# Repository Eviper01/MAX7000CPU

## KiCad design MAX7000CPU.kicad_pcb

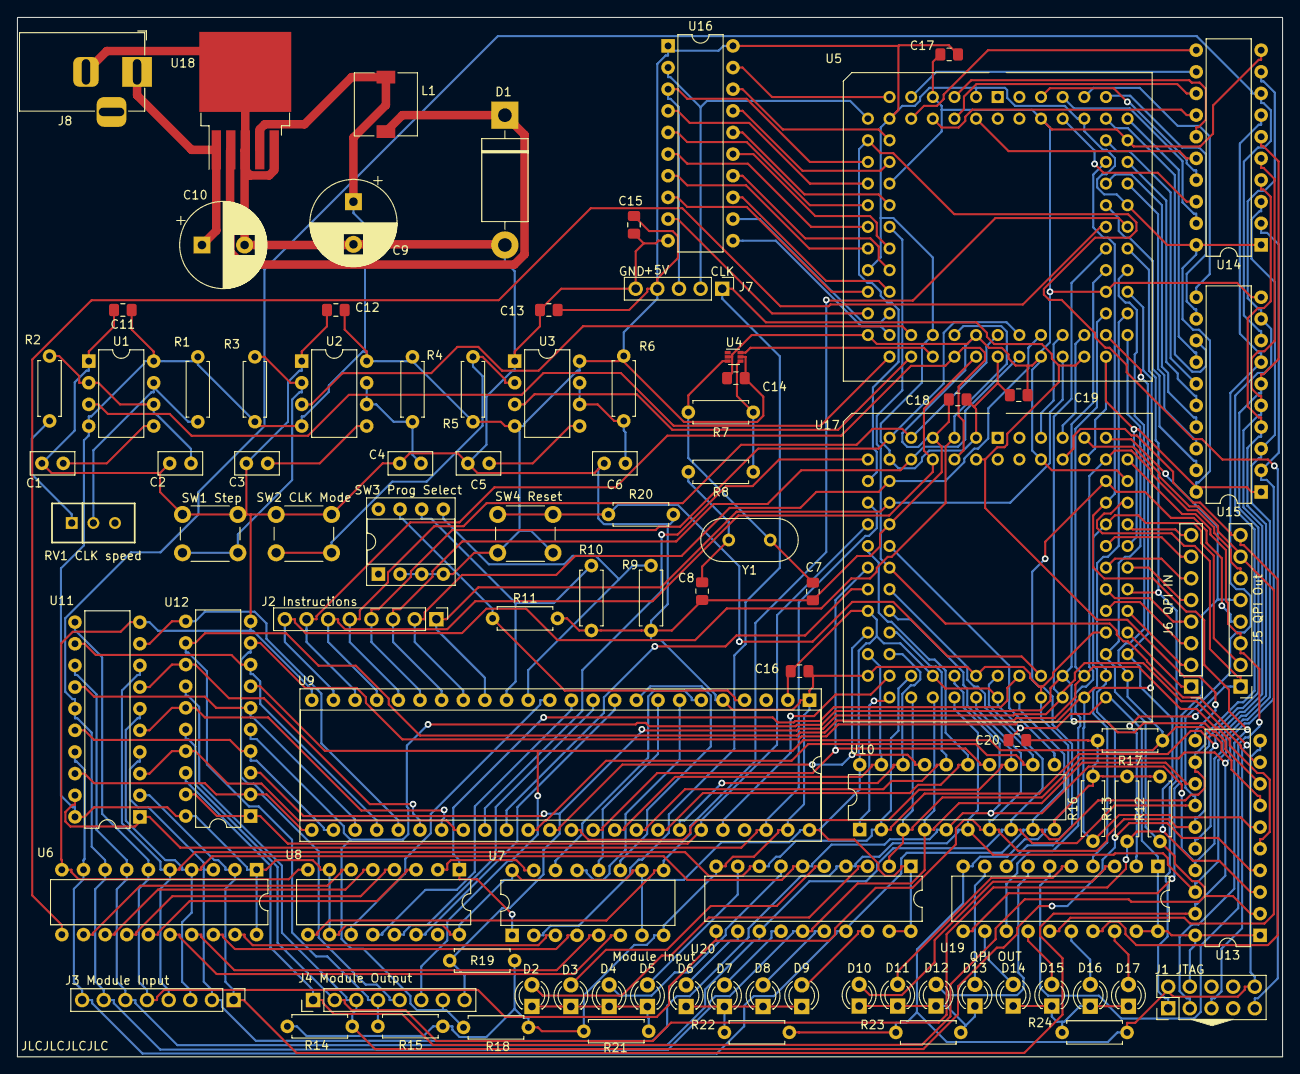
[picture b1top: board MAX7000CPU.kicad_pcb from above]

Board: 2 copper layers, 148.5 x 122.0 mm, 96 parts (0 on the bottom side), 170 nets.

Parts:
C1, C2, C3, C5: 10n; C_Disc_D5.0mm_W2.5mm_P2.50mm
C4, C6: 100n; C_Disc_D5.0mm_W2.5mm_P2.50mm
C7, C8: 32p; C_0805_2012Metric_Pad1.18x1.45mm_HandSolder
C9: 220u; CP_Radial_D10.0mm_P5.00mm
C10: 680u; CP_Radial_D10.0mm_P5.00mm
C11, C12, C13, C14, C15, C16, C17, C18, C19, C20: 100n; C_0805_2012Metric_Pad1.18x1.45mm_HandSolder
D1: 1N5822; D_DO-201AD_P15.24mm_Horizontal
D2, D3, D4, D5, D6, D7, D8, D9, D10, D11, D12, D13, D14, D15, D16, D17: LED; LED_D3.0mm
J1 JTAG: Conn_02x05_Odd_Even; PinHeader_2x05_P2.54mm_Vertical
J2 Instructions, J3 Module Input, J4 Module Output, J5 QPI Out, J6 QPI IN: Conn_01x08_Male; PinHeader_1x08_P2.54mm_Vertical
J7: Conn_01x05_Male; PinHeader_1x05_P2.54mm_Vertical
J8: Barrel_Jack; BarrelJack_Horizontal
L1: 33u; L_7.3x7.3_H3.5
R1, R2, R3, R5, R8: 1K; R_Axial_DIN0207_L6.3mm_D2.5mm_P7.62mm_Horizontal
R4, R6: 1M; R_Axial_DIN0207_L6.3mm_D2.5mm_P7.62mm_Horizontal
R7: 2.2M; R_Axial_DIN0207_L6.3mm_D2.5mm_P7.62mm_Horizontal
R9, R10, R11, R12, R13, R14, R15, R16, R17, R18, R19, R20: 50K; R_Axial_DIN0207_L6.3mm_D2.5mm_P7.62mm_Horizontal
R21, R22, R23, R24: 200; R_Axial_DIN0207_L6.3mm_D2.5mm_P7.62mm_Horizontal
RV1 CLK speed: 1M; SIP460W50P254L970H980Q3P
SW1 Step, SW2 CLK Mode, SW4 Reset: SW_Push; SW_PUSH_6mm
SW3 Prog Select: SW_DIP_x04; DIP-8_W7.62mm_Socket
U1, U2, U3: NE555P; DIP-8_W7.62mm
U4: CLVC1GX04MDRLREP; SOT-563
U5, U17: EPM7128slc84-15n; PLCC-84_THT-Socket
U6, U10, U13, U14, U15, U16: 74LS573; DIP-20_W7.62mm
U7, U8: SN74HC161N; DIP-16_W7.62mm
U9: IDT7132; DIP-48_W15.24mm_Socket
U11, U12, U19, U20: 74LS241; DIP-20_W7.62mm
U18: LM2596S-5; TO-263-5_TabPin3
Y1: Crystal; Crystal_HC49-4H_Vertical

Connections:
+5V: C9.1, C11.1, C12.1, C13.1, C14.1, C15.1, C16.1, C17.1, C18.1, C19.1, C20.1, J1 JTAG.4, J7.4, L1.1, R1.1, R3.1, R4.1, R5.1, R6.1, SW3 Prog Select.2, SW3 Prog Select.3, SW3 Prog Select.4, SW4 Reset.2, U1.4, U1.8, U2.4, U2.8, U3.4, U3.8, U4.5, U5.3, U5.13, U5.26, U5.38, U5.43, U5.53, U5.66, U5.78, U6.1, U6.20, U7.7, U7.10, U7.16, U8.7, U8.10, U8.16, U9.2, U9.48, U10.20, U11.20, U12.20, U13.1, U13.20, U14.1, U14.20, U15.1, U15.20, U16.1, U16.20, U17.3, U17.13, U17.26, U17.38, U17.43, U17.53, U17.66, U17.78, U18.4, U19.1, U19.19, U19.20, U20.1, U20.19, U20.20
/A0: U5.79, U14.19
/A1: U5.80, U14.18
/A2: U5.81, U14.17
/A3: U5.4, U14.16
/A4: U5.5, U14.15
/A5: U5.8, U14.14
/A6: U5.6, U14.13
/A7: U5.9, U14.12
/B0: U5.67, U15.19
/B1: U5.68, U15.18
/B2: U5.69, U15.17
/B3: U5.70, U15.16
/B4: U5.73, U15.15
/B5: U5.74, U15.14
/B6: U5.76, U15.13
/B7: U5.75, U15.12
/C0: U7.14, U9.6
/C1: U7.13, U9.7
/C2: U7.12, U9.8
/C3: U7.11, U9.9
/C4: U8.14, U9.10
/C5: U8.13, U9.11
/C6: U8.12, U9.12
/C7: U8.11, U9.13
/I0: J3 Module Input.1, U6.2, U10.3, U11.2, U13.19, U14.2, U15.2, U17.35, U20.2
/I1: J3 Module Input.2, U6.3, U10.6, U11.4, U13.18, U14.3, U15.3, U17.39, U20.4
/I2: J3 Module Input.3, U6.4, U10.5, U11.6, U13.17, U14.4, U15.4, U17.40, U20.6
/I3: J3 Module Input.4, U6.5, U10.2, U11.8, U13.16, U14.5, U15.5, U17.36, U20.8
/I4: J3 Module Input.5, U6.6, U10.7, U11.11, U13.15, U14.6, U15.6, U17.41, U20.11
/I5: J3 Module Input.6, U6.7, U10.8, U11.13, U13.14, U14.7, U15.7, U17.44, U20.13
/I6: J3 Module Input.7, U6.8, U10.4, U11.15, U13.13, U14.8, U15.8, U17.37, U20.15
/I7: J3 Module Input.8, U6.9, U10.9, U11.17, U13.12, U14.9, U15.9, U17.45, U20.17
/Im0: D9.2, U20.18
/Im1: D8.2, U20.16
/Im2: D7.2, U20.14
/Im3: D6.2, U20.12
/Im4: D5.2, U20.9
/Im5: D4.2, U20.7
/Im6: D3.2, U20.5
/Im7: D2.2, U20.3
/Ins0: J2 Instructions.1, U5.49, U9.16, U17.17
/Ins1: J2 Instructions.2, U5.48, U9.17, U17.15
/Ins2: J2 Instructions.3, U5.45, U9.18, U17.10
/Ins3: J2 Instructions.4, U5.46, U9.19, U17.11
/Ins4: J2 Instructions.5, U5.44, U9.20, U17.9
/Ins5: J2 Instructions.6, U5.41, U9.21, U17.8
/Ins6: J2 Instructions.7, U5.39, U9.22, U17.6
/Ins7: J2 Instructions.8, U5.40, U9.23, U17.5
/Iq0: D17.2, U19.18
/Iq1: D16.2, U19.16
/Iq2: D15.2, U19.14
/Iq3: D14.2, U19.12
/Iq4: D13.2, U19.9
/Iq5: D12.2, U19.7
/Iq6: D11.2, U19.5
/Iq7: D10.2, U19.3
/M0: U9.42, U10.18, U17.31
/M1: U9.41, U10.15, U17.20
/M2: U9.40, U10.16, U17.29
/M3: U9.39, U10.19, U17.30
/M4: U9.38, U10.14, U17.22
/M5: U9.37, U10.13, U17.27
/M6: U9.36, U10.17, U17.28
/M7: U9.35, U10.12, U17.25
/M8: U9.34, U17.24
/M9: U9.33, U17.12
/M10: U9.44, U17.34
/O0: J4 Module Output.1, R12.1, U5.54, U12.18, U13.2, U17.57
/O1: J4 Module Output.2, R13.1, U5.55, U12.16, U13.3, U17.56
/O2: J4 Module Output.3, R14.1, U5.56, U12.14, U13.4, U17.55
/O3: J4 Module Output.4, R15.1, U5.57, U12.12, U13.5, U17.52
/O4: J4 Module Output.5, R16.1, U5.58, U12.9, U13.6, U17.51
/O5: J4 Module Output.6, R17.1, U5.60, U12.7, U13.7, U17.54
/O6: J4 Module Output.7, R18.1, U5.61, U12.5, U13.8, U17.50
/O7: J4 Module Output.8, R19.1, U5.63, U12.3, U13.9, U17.49
/P1: R9.1, SW3 Prog Select.5, U9.14
/P2: R10.1, SW3 Prog Select.6, U9.15
/P3: R11.1, SW3 Prog Select.7, U9.4
/Qi0: J6 QPI IN.1, U17.58
/Qi1: J6 QPI IN.2, U17.60
/Qi2: J6 QPI IN.3, U17.61
/Qi3: J6 QPI IN.4, U17.63
/Qi4: J6 QPI IN.5, U17.64
/Qi5: J6 QPI IN.6, U17.65
/Qi6: J6 QPI IN.7, U17.67
/Qi7: J6 QPI IN.8, U17.68
/Qo0: J5 QPI Out.1, U17.70, U19.2
/Qo1: J5 QPI Out.2, U17.69, U19.4
/Qo2: J5 QPI Out.3, U17.74, U19.6
/Qo3: J5 QPI Out.4, U17.73, U19.8
/Qo4: J5 QPI Out.5, U17.75, U19.11
/Qo5: J5 QPI Out.6, U17.76, U19.13
/Qo6: J5 QPI Out.7, U17.77, U19.15
/Qo7: J5 QPI Out.8, U17.80, U19.17
A=B_FlagIn: U5.15, U16.18
A=B_Out: J7.3, U5.16, U16.3
CLK: J7.1, U5.51, U7.2, U13.11, U17.4
CLK_Select: U3.3, U5.35
CarryFlagIn: U5.11, U16.19
CarryOut: J7.2, U5.12, U16.2
Comm0: U5.50, U17.81
Comm1: U5.52, U17.79
CounterReset: U7.1, U8.1, U17.46
FastCLK: U4.6, U5.37
Flag0In: U5.17, U16.17
Flag0Out: U5.18, U16.4
Flag1In: U5.21, U16.16
Flag1Out: U5.20, U16.5
Flag2In: U5.25, U16.15
Flag2Out: U5.22, U16.6
Flag3In: U5.27, U16.14
Flag3Out: U5.24, U16.7
Flag4In: U5.29, U16.13
Flag4Out: U5.28, U16.8
Flag5In: U5.31, U16.12
Flag5Out: U5.30, U16.9
FlagCLK: U5.34, U16.11
GND: C1.2, C2.2, C3.2, C4.2, C5.2, C6.2, C7.2, C8.2, C9.2, C10.2, C11.2, C12.2, C13.2, C14.2, C15.2, C16.2, C17.2, C18.2, C19.2, C20.2, D1.2, J1 JTAG.2, J1 JTAG.10, J7.5, J8.2, R9.2, R10.2, R11.2, R12.2, R13.2, R14.2, R15.2, R16.2, R17.2, R18.2, R19.2, R20.2, R21.2, R22.2, R23.2, R24.2, SW1 Step.1, SW2 CLK Mode.1, U1.1, U2.1, U3.1, U4.2, U5.7, U5.19, U5.32, U5.42, U5.47, U5.59, U5.72, U5.82, U6.10, U7.8, U8.8, U9.1, U9.5, U9.24, U9.47, U10.10, U11.10, U12.10, U13.10, U14.10, U15.10, U16.10, U17.7, U17.19, U17.32, U17.42, U17.47, U17.59, U17.72, U17.82, U18.3, U18.5, U19.10, U20.10
JumpEnable: U5.64, U7.9, U8.9
JumpRegLoad: U5.65, U6.11
MemOutControl: U9.43, U12.1, U12.19, U17.18
MemWriteControl: U9.46, U11.1, U11.19, U17.16
unnamed: C1.1, U1.5
unnamed: C2.1, R2.2, U1.2, U1.6
unnamed: C3.1, U2.5
unnamed: C4.1, R4.2, U2.6, U2.7
unnamed: C5.1, U3.5
unnamed: C6.1, R6.2, U3.6, U3.7
unnamed: C7.1, R7.2, U4.3, Y1.1
unnamed: C8.1, R8.2, Y1.2
unnamed: C10.1, J8.1, U18.1
unnamed: D1.1, L1.2, U18.2
unnamed: D2.1, D3.1, D4.1, D5.1, R21.1
unnamed: D6.1, D7.1, D8.1, D9.1, R22.1
unnamed: D10.1, D11.1, D12.1, D13.1, R23.1
unnamed: D14.1, D15.1, D16.1, D17.1, R24.1
unnamed: R1.2, RV1 CLK speed.2, U1.7
unnamed: R2.1, RV1 CLK speed.1
unnamed: R3.2, SW1 Step.2, U2.2
unnamed: R5.2, SW2 CLK Mode.2, U3.2
unnamed: R7.1, R8.1, U4.4
unnamed: U6.12, U8.6
unnamed: U6.13, U8.5
unnamed: U6.14, U8.4
unnamed: U6.15, U8.3
unnamed: U6.16, U7.6
unnamed: U6.17, U7.5
unnamed: U6.18, U7.4
unnamed: U6.19, U7.3
unnamed: U7.15, U8.2
unnamed: U9.32, U11.3, U12.17
unnamed: U9.31, U11.5, U12.15
unnamed: U9.30, U11.7, U12.13
unnamed: U9.29, U11.9, U12.11
unnamed: U9.28, U11.12, U12.8
unnamed: U9.27, U11.14, U12.6
unnamed: U9.26, U11.16, U12.4
unnamed: U9.25, U11.18, U12.2
RamAddrEnable: U10.1, U17.33
RamAddrLoad: U10.11, U17.21
RegAControl: U5.10, U14.11
RegBControl: U5.77, U15.11
Reset: R20.1, SW4 Reset.1, U17.48
SlowCLK: U1.3, U5.33
TCK: J1 JTAG.1, U5.62, U17.62
TDI: J1 JTAG.9, U5.14, U17.14
TDO: J1 JTAG.3, U5.71, U17.71
TMS: J1 JTAG.5, U5.23, U17.23
UserCLK: U2.3, U5.36

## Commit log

2021-09-03 misc updatees
2021-09-03 auto routed
